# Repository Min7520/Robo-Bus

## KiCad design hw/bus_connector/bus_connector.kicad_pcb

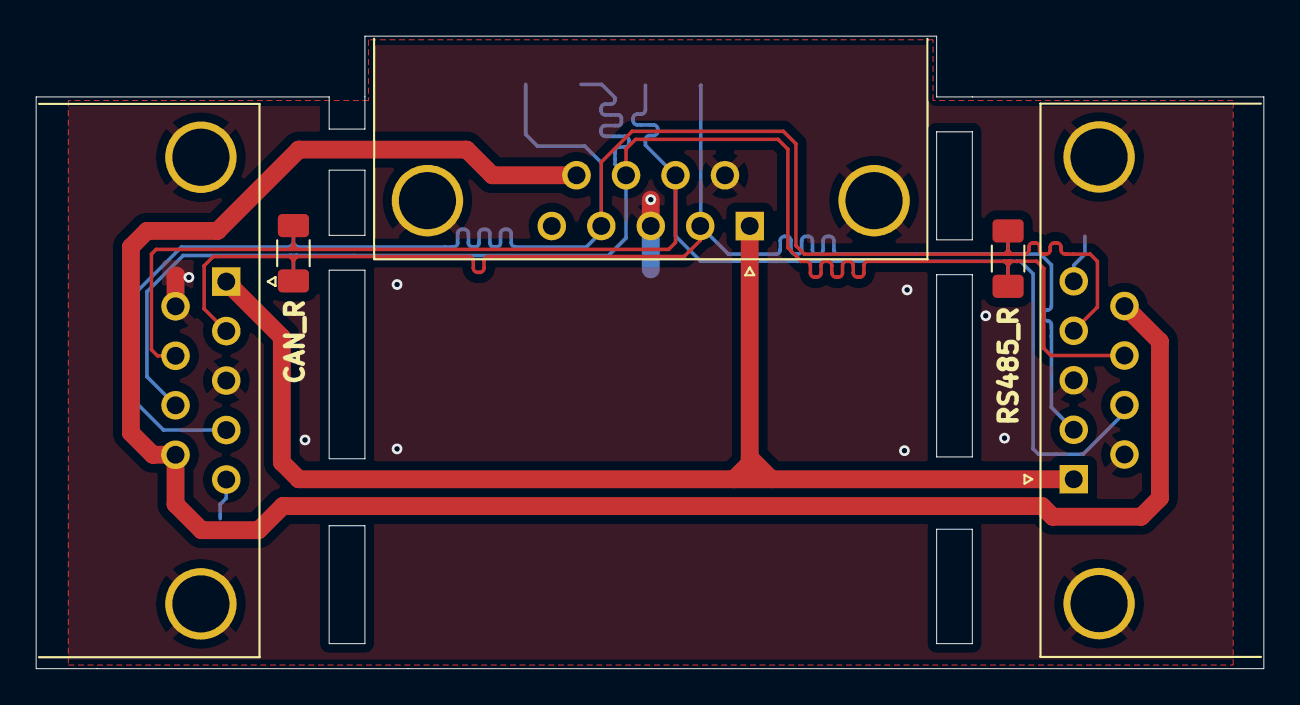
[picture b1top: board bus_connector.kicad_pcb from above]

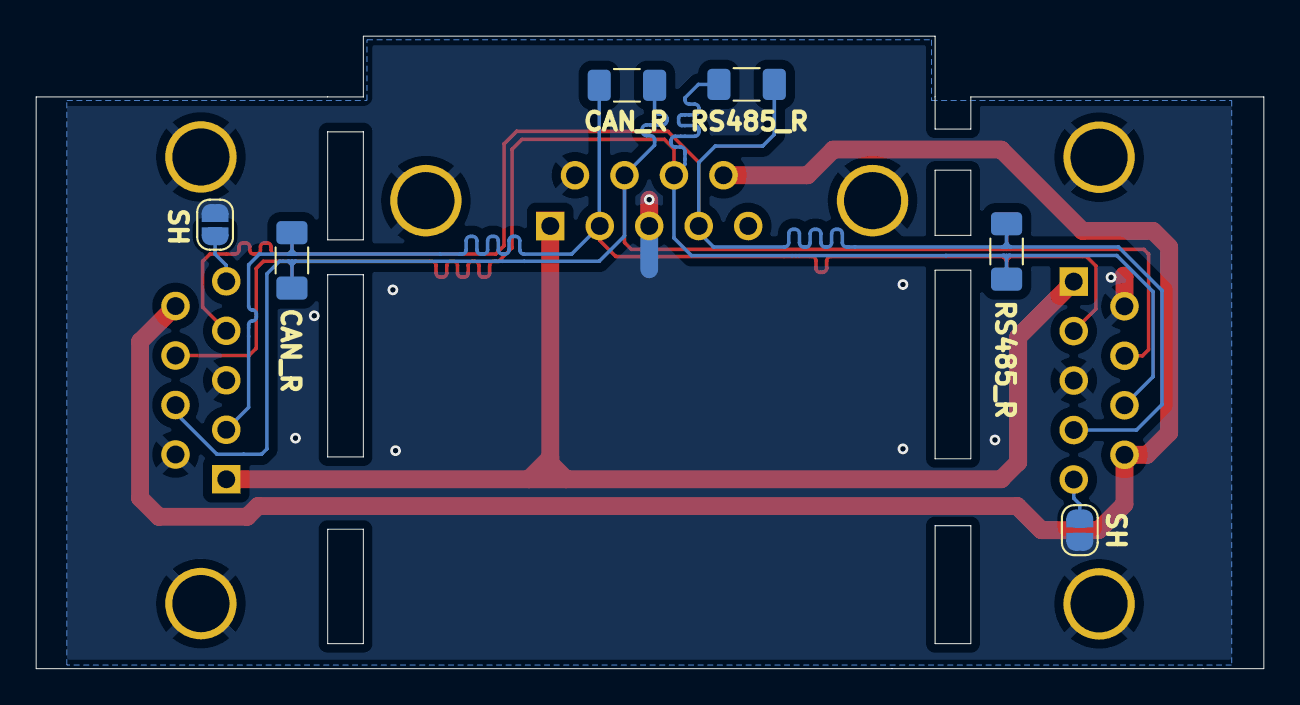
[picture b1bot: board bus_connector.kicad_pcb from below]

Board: 2 copper layers, 68.7 x 35.4 mm, 11 parts (6 on the bottom side), 8 nets.

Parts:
J1: DB9_Top; DSUB-9_Pins_Horizontal_P2.77x2.84mm_EdgePinOffset7.70mm_Hou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
J2: DB9_Left; DSUB-9_Pins_Horizontal_P2.77x2.84mm_EdgePinOffset7.70mm_Hou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
J3: DB9_Right; DSUB-9_Pins_Horizontal_P2.77x2.84mm_EdgePinOffset7.70mm_Hou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
JP1, JP3: Shield_JMP; SolderJumper-2_P1.3mm_Open_RoundedPad1.0x1.5mm
R1, R2, R3, R4, R5, R6: 120; R_1206_3216Metric_Pad1.30x1.75mm_HandSolder

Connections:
CAN+: J1.7, J2.7, J3.7, R2.2, R4.2, R6.2
CAN-: J1.2, J2.2, J3.2, R2.1, R4.1, R6.1
GND: J1.0 (PAD), J1.3, J1.6, J2.0 (PAD), J2.3, J2.6, J3.0 (PAD), J3.3, J3.6, JP1.2 (B), JP3.2 (B)
MODBUS+: J1.8, J2.8, J3.8, R1.2, R3.2, R5.2
MODBUS-: J1.4, J2.4, J3.4, R1.1, R3.1, R5.1
SHIELD_L: J2.5, JP1.1 (A)
SHIELD_R: J3.5, JP3.1 (A)
VCC: J1.1, J1.9, J2.1, J2.9, J3.1, J3.9

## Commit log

2025-11-12 Add initial bus connector schematic
2025-11-12 AUTO: Update reports
